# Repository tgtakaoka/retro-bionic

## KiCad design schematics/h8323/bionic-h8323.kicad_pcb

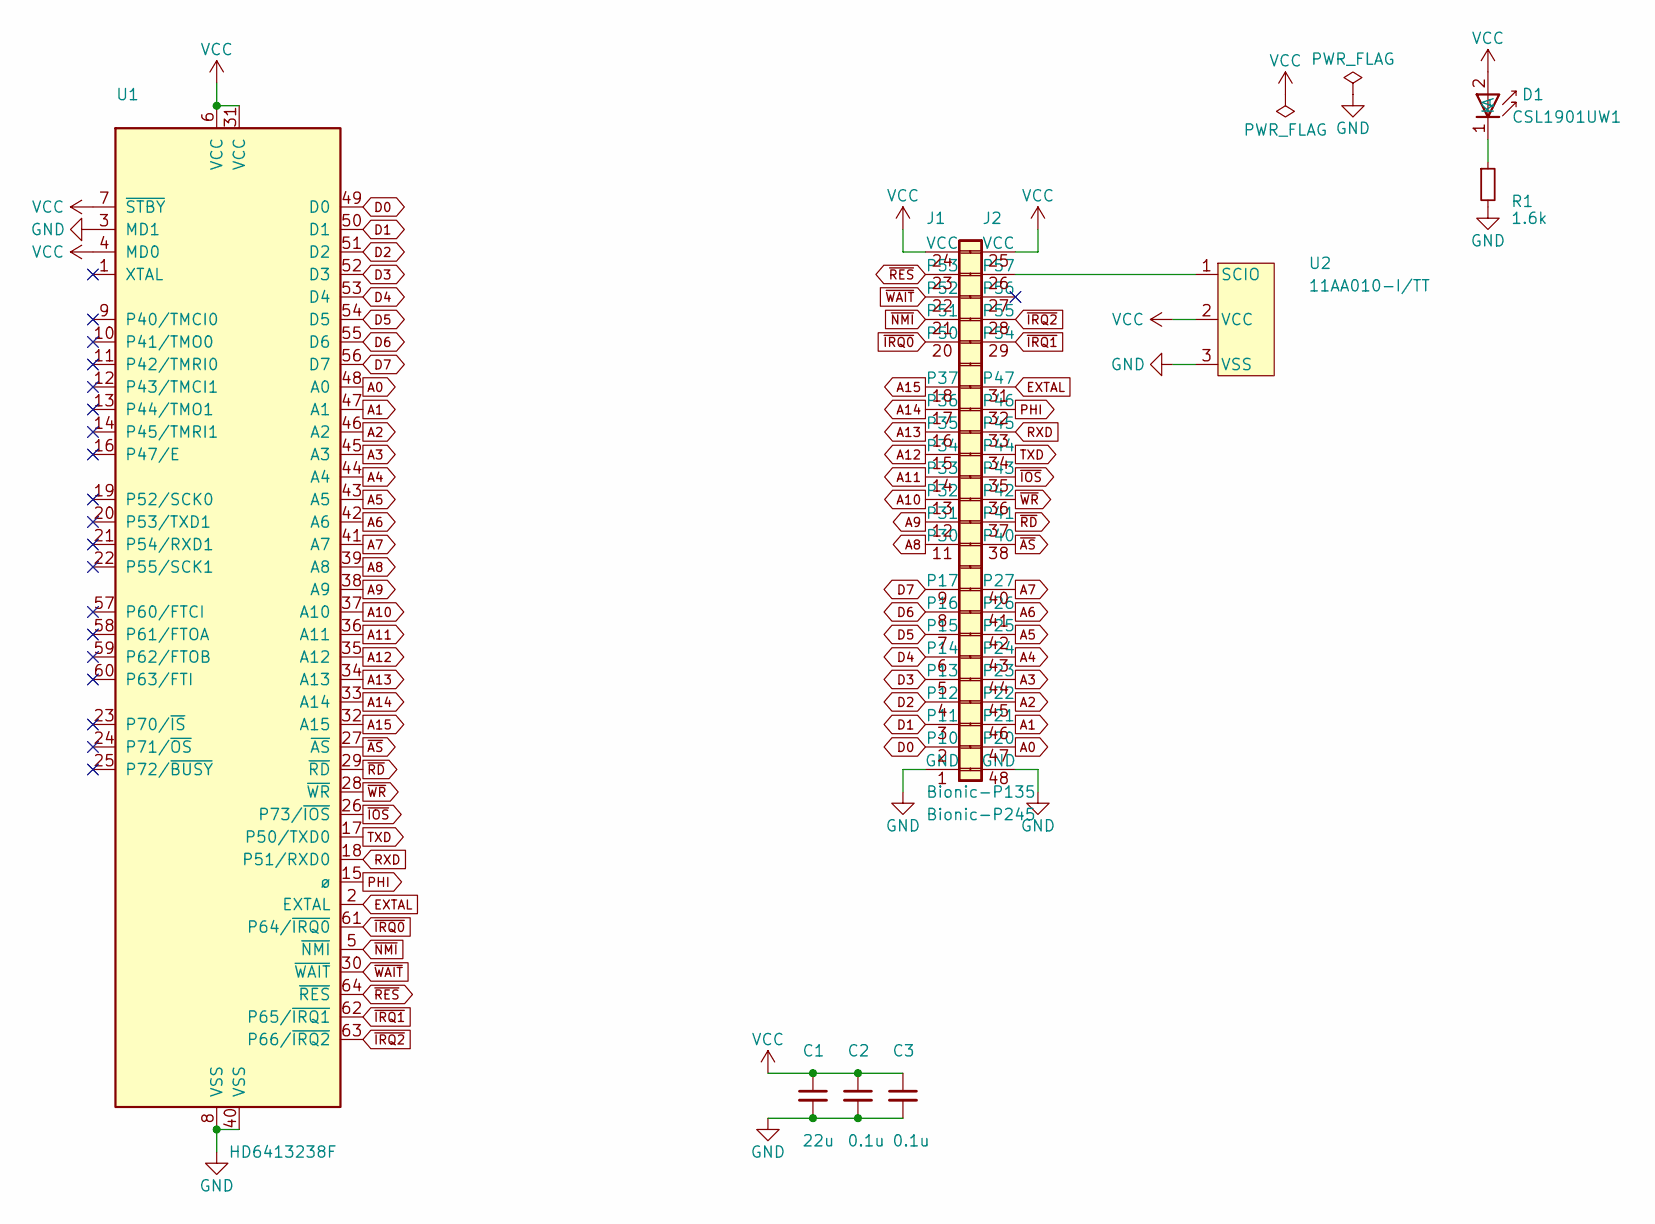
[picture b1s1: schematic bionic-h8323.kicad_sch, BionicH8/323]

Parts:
C1: 22u; C_0603_1608Metric_Pad1.08x0.95mm_HandSolder
C2, C3: 0.1u; C_0603_1608Metric_Pad1.08x0.95mm_HandSolder
D1: CSL1901UW1; LED_CSL1901UW1_ROM-M
J1: Bionic-P135; Bionic-P135_SMT
J2: Bionic-P245; Bionic-P245_SMT
R1: 1.6k; R_0603_1608Metric_Pad0.98x0.95mm_HandSolder
U1: HD6413238F; QFP-64_14x14mm_P0.8mm_Hitachi
U2: 11AA010-I/TT; SOT-23_MC_MCH-M

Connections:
A0: J2.47 (P20), U1.48 (A0)
A1: J2.46 (P21), U1.47 (A1)
A2: J2.45 (P22), U1.46 (A2)
A3: J2.44 (P23), U1.45 (A3)
A4: J2.43 (P24), U1.44 (A4)
A5: J2.42 (P25), U1.43 (A5)
A6: J2.41 (P26), U1.42 (A6)
A7: J2.40 (P27), U1.41 (A7)
A8: J1.11 (P30), U1.39 (A8)
A9: J1.12 (P31), U1.38 (A9)
A10: J1.13 (P32), U1.37 (A10)
A11: J1.14 (P33), U1.36 (A11)
A12: J1.15 (P34), U1.35 (A12)
A13: J1.16 (P35), U1.34 (A13)
A14: J1.17 (P36), U1.33 (A14)
A15: J1.18 (P37), U1.32 (A15)
D0: J1.2 (P10), U1.49 (D0)
D1: J1.3 (P11), U1.50 (D1)
D2: J1.4 (P12), U1.51 (D2)
D3: J1.5 (P13), U1.52 (D3)
D4: J1.6 (P14), U1.53 (D4)
D5: J1.7 (P15), U1.54 (D5)
D6: J1.8 (P16), U1.55 (D6)
D7: J1.9 (P17), U1.56 (D7)
EXTAL: J2.31 (P47), U1.2 (EXTAL)
GND: C1.2, C2.2, C3.2, J1.1 (GND), J2.48 (GND), R1.2, U1.3 (MD1), U1.8 (VSS), U1.40 (VSS), U2.3 (VSS)
unnamed: D1.1 (K), R1.1
unnamed: J2.26 (P57), U2.1 (SCIO)
PHI: J2.32 (P46), U1.15 (ø)
RXD: J2.33 (P45), U1.18 (P51/RXD0)
TXD: J2.34 (P44), U1.17 (P50/TXD0)
VCC: C1.1, C2.1, C3.1, D1.2 (A), J1.24 (VCC), J2.25 (VCC), U1.4 (MD0), U1.6 (VCC), U1.7 (~STBY), U1.31 (VCC), U2.2 (VCC)
~AS: J2.38 (P40), U1.27 (~AS)
~IOS: J2.35 (P43), U1.26 (P73/~IOS)
~IRQ0: J1.20 (P50), U1.61 (P64/~IRQ0)
~IRQ1: J2.29 (P54), U1.62 (P65/~IRQ1)
~IRQ2: J2.28 (P55), U1.63 (P66/~IRQ2)
~NMI: J1.21 (P51), U1.5 (~NMI)
~RD: J2.37 (P41), U1.29 (~RD)
~RES: J1.23 (P53), U1.64 (~RES)
~WAIT: J1.22 (P52), U1.30 (~WAIT)
~WR: J2.36 (P42), U1.28 (~WR)

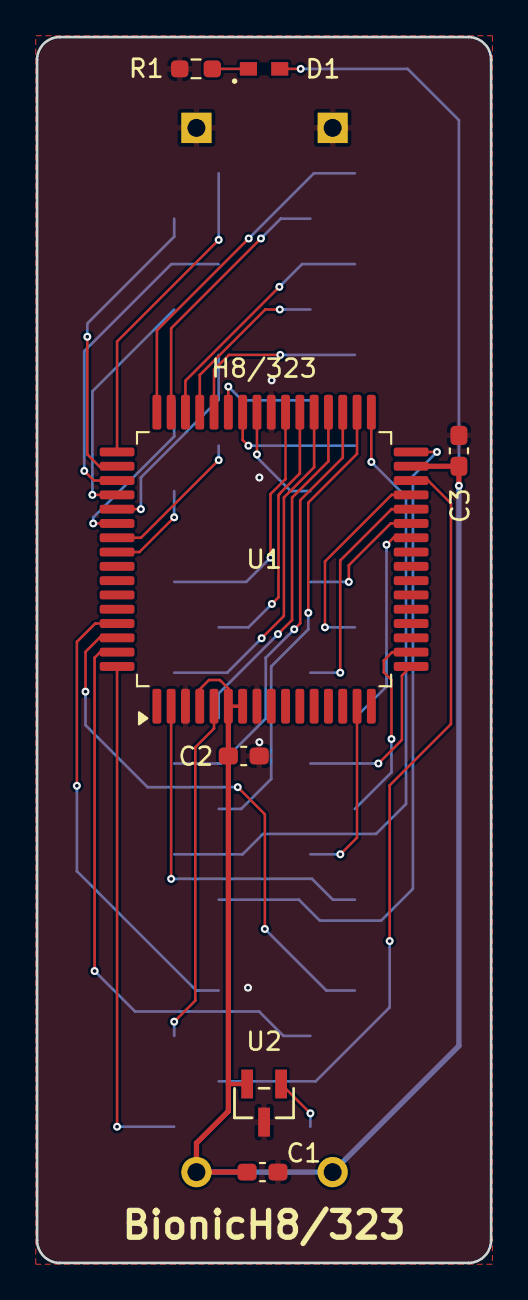
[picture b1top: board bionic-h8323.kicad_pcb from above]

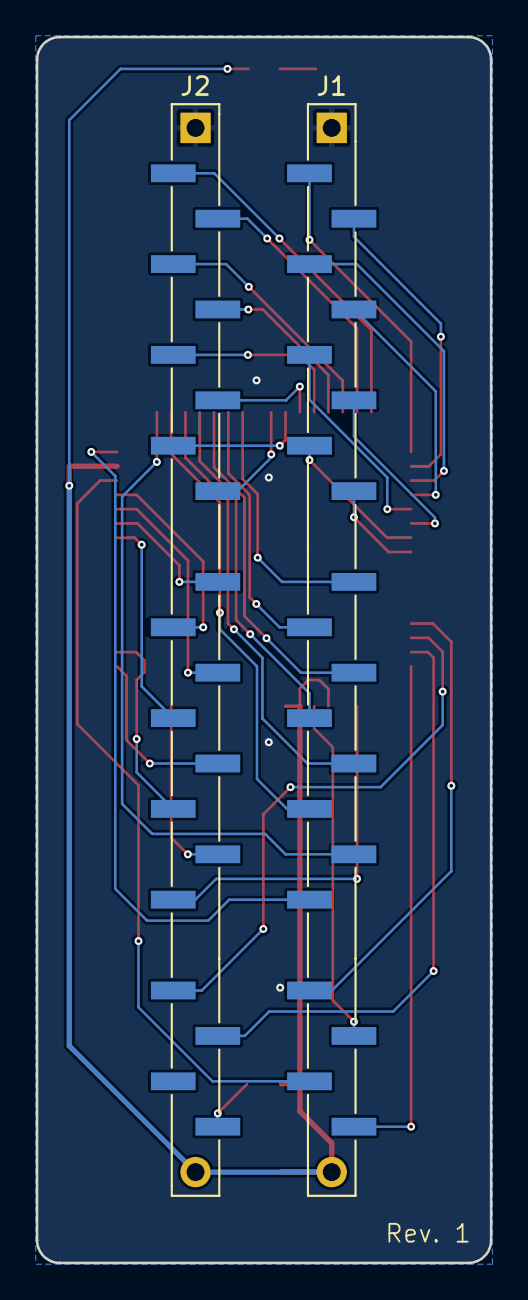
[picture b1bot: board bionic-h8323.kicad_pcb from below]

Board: 2 copper layers, 25.4 x 68.6 mm, 9 parts (2 on the bottom side), 42 nets.

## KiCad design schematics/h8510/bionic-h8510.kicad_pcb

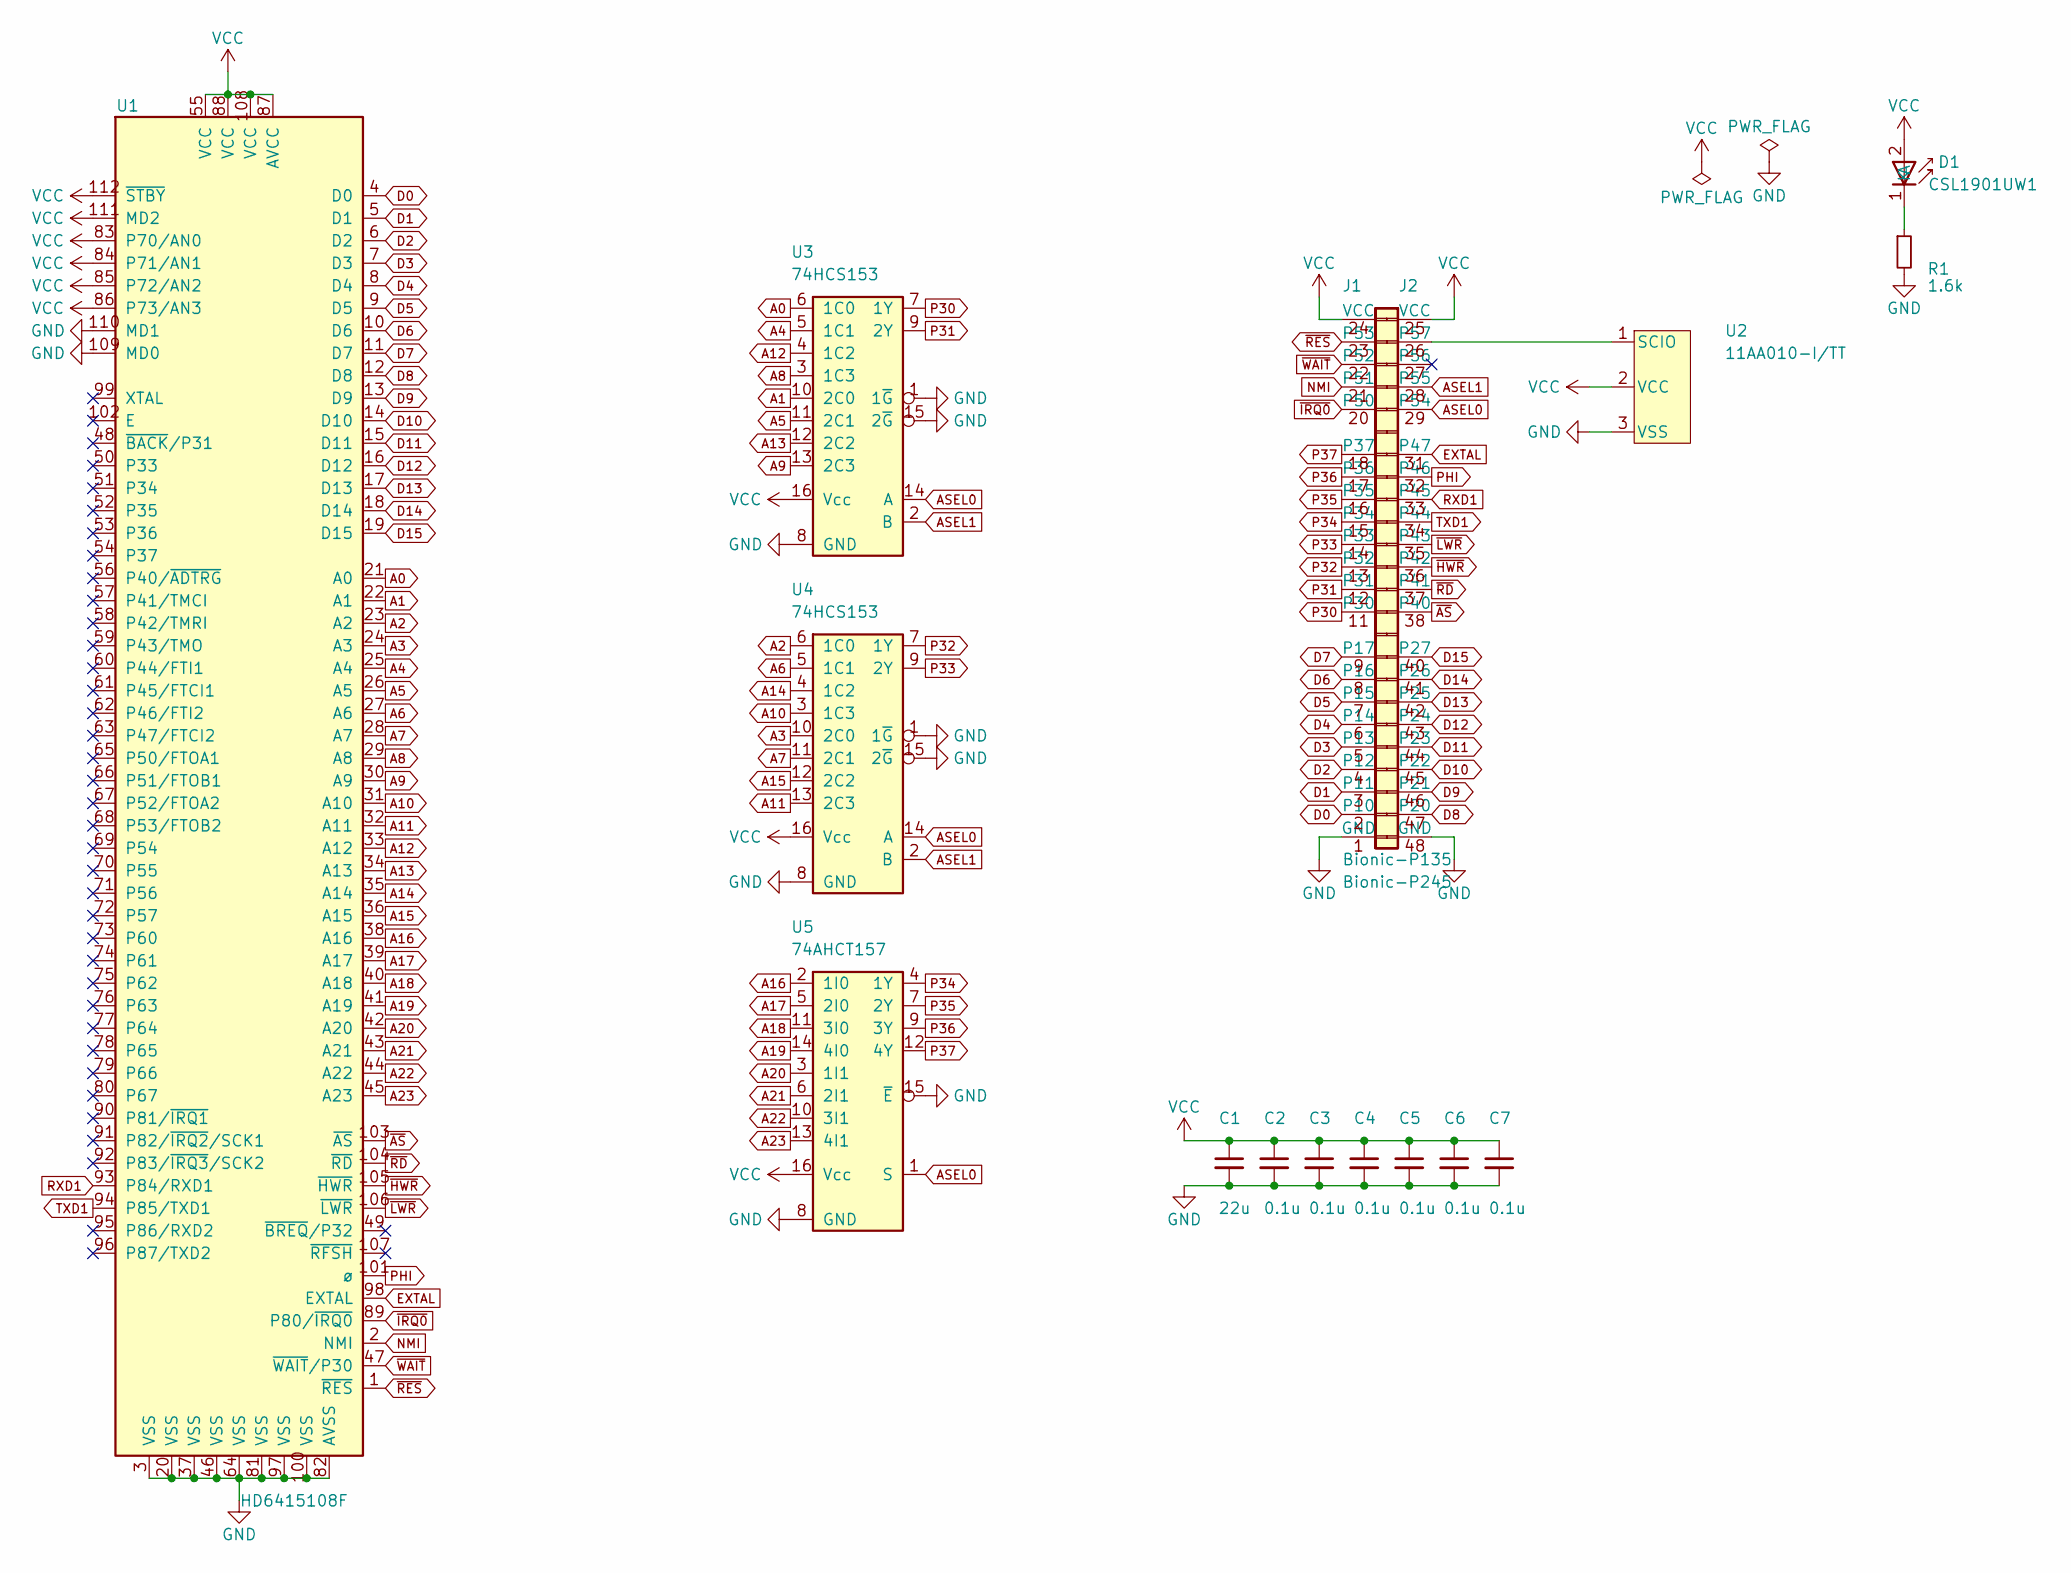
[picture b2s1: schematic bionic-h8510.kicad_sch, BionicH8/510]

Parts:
C1: 22u; C_0603_1608Metric_Pad1.08x0.95mm_HandSolder
C2, C3, C4, C5, C6, C7: 0.1u; C_0603_1608Metric_Pad1.08x0.95mm_HandSolder
D1: CSL1901UW1; LED_CSL1901UW1_ROM-M
J1: Bionic-P135; Bionic-P135_SMT
J2: Bionic-P245; Bionic-P245_SMT
R1: 1.6k; R_0603_1608Metric_Pad0.98x0.95mm_HandSolder
U1: HD6415108F; QFP-112_20x20mm_P0.65mm_Hitachi
U2: 11AA010-I/TT; SOT-23_MC_MCH-M
U3, U4: 74HCS153; PW16-M
U5: 74AHCT157; PW16-M

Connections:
A0: U1.21 (A0), U3.6 (1C0)
A1: U1.22 (A1), U3.10 (2C0)
A2: U1.23 (A2), U4.6 (1C0)
A3: U1.24 (A3), U4.10 (2C0)
A4: U1.25 (A4), U3.5 (1C1)
A5: U1.26 (A5), U3.11 (2C1)
A6: U1.27 (A6), U4.5 (1C1)
A7: U1.28 (A7), U4.11 (2C1)
A8: U1.29 (A8), U3.3 (1C3)
A9: U1.30 (A9), U3.13 (2C3)
A10: U1.31 (A10), U4.3 (1C3)
A11: U1.32 (A11), U4.13 (2C3)
A12: U1.33 (A12), U3.4 (1C2)
A13: U1.34 (A13), U3.12 (2C2)
A14: U1.35 (A14), U4.4 (1C2)
A15: U1.36 (A15), U4.12 (2C2)
A16: U1.38 (A16), U5.2 (1I0)
A17: U1.39 (A17), U5.5 (2I0)
A18: U1.40 (A18), U5.11 (3I0)
A19: U1.41 (A19), U5.14 (4I0)
A20: U1.42 (A20), U5.3 (1I1)
A21: U1.43 (A21), U5.6 (2I1)
A22: U1.44 (A22), U5.10 (3I1)
A23: U1.45 (A23), U5.13 (4I1)
ASEL0: J2.29 (P54), U3.14 (A), U4.14 (A), U5.1 (S)
ASEL1: J2.28 (P55), U3.2 (B), U4.2 (B)
D0: J1.2 (P10), U1.4 (D0)
D1: J1.3 (P11), U1.5 (D1)
D2: J1.4 (P12), U1.6 (D2)
D3: J1.5 (P13), U1.7 (D3)
D4: J1.6 (P14), U1.8 (D4)
D5: J1.7 (P15), U1.9 (D5)
D6: J1.8 (P16), U1.10 (D6)
D7: J1.9 (P17), U1.11 (D7)
D8: J2.47 (P20), U1.12 (D8)
D9: J2.46 (P21), U1.13 (D9)
D10: J2.45 (P22), U1.14 (D10)
D11: J2.44 (P23), U1.15 (D11)
D12: J2.43 (P24), U1.16 (D12)
D13: J2.42 (P25), U1.17 (D13)
D14: J2.41 (P26), U1.18 (D14)
D15: J2.40 (P27), U1.19 (D15)
EXTAL: J2.31 (P47), U1.98 (EXTAL)
GND: C1.2, C2.2, C3.2, C4.2, C5.2, C6.2, C7.2, J1.1 (GND), J2.48 (GND), R1.2, U1.3 (VSS), U1.20 (VSS), U1.37 (VSS), U1.46 (VSS), U1.64 (VSS), U1.81 (VSS), U1.82 (AVSS), U1.97 (VSS), U1.100 (VSS), U1.109 (MD0), U1.110 (MD1), U2.3 (VSS), U3.1 (1~G), U3.8 (GND), U3.15 (2~G), U4.1 (1~G), U4.8 (GND), U4.15 (2~G), U5.8 (GND), U5.15 (~E)
NMI: J1.21 (P51), U1.2 (NMI)
unnamed: D1.1 (K), R1.1
unnamed: J2.26 (P57), U2.1 (SCIO)
P30: J1.11 (P30), U3.7 (1Y)
P31: J1.12 (P31), U3.9 (2Y)
P32: J1.13 (P32), U4.7 (1Y)
P33: J1.14 (P33), U4.9 (2Y)
P34: J1.15 (P34), U5.4 (1Y)
P35: J1.16 (P35), U5.7 (2Y)
P36: J1.17 (P36), U5.9 (3Y)
P37: J1.18 (P37), U5.12 (4Y)
PHI: J2.32 (P46), U1.101 (ø)
RXD1: J2.33 (P45), U1.93 (P84/RXD1)
TXD1: J2.34 (P44), U1.94 (P85/TXD1)
VCC: C1.1, C2.1, C3.1, C4.1, C5.1, C6.1, C7.1, D1.2 (A), J1.24 (VCC), J2.25 (VCC), U1.55 (VCC), U1.83 (P70/AN0), U1.84 (P71/AN1), U1.85 (P72/AN2), U1.86 (P73/AN3), U1.87 (AVCC), U1.88 (VCC), U1.108 (VCC), U1.111 (MD2), U1.112 (~STBY), U2.2 (VCC), U3.16 (Vcc), U4.16 (Vcc), U5.16 (Vcc)
~AS: J2.38 (P40), U1.103 (~AS)
~HWR: J2.36 (P42), U1.105 (~HWR)
~IRQ0: J1.20 (P50), U1.89 (P80/~IRQ0)
~LWR: J2.35 (P43), U1.106 (~LWR)
~RD: J2.37 (P41), U1.104 (~RD)
~RES: J1.23 (P53), U1.1 (~RES)
~WAIT: J1.22 (P52), U1.47 (~WAIT/P30)

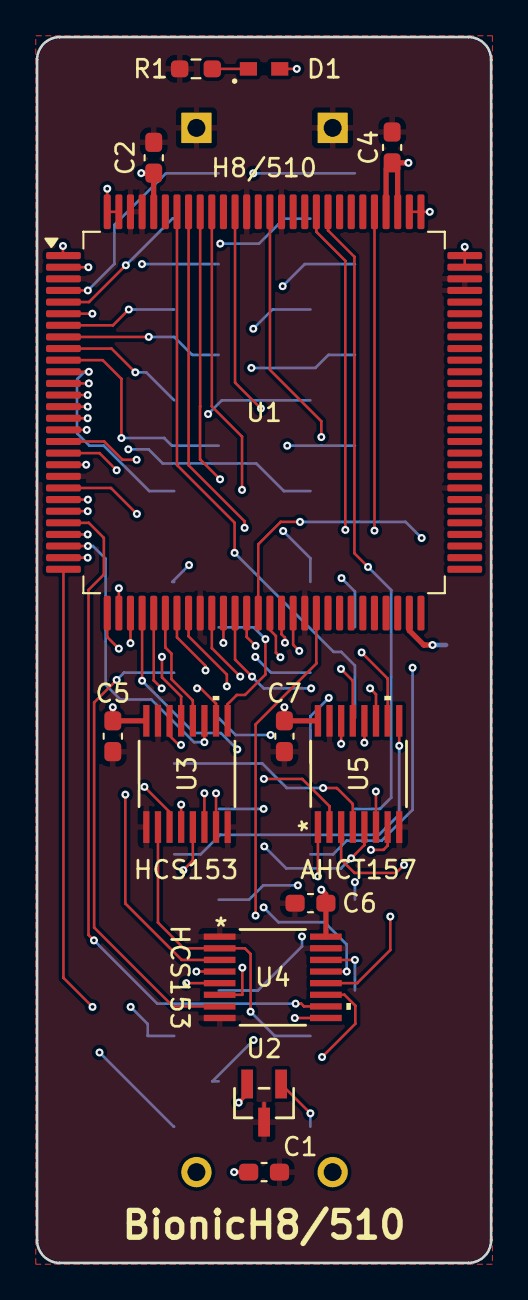
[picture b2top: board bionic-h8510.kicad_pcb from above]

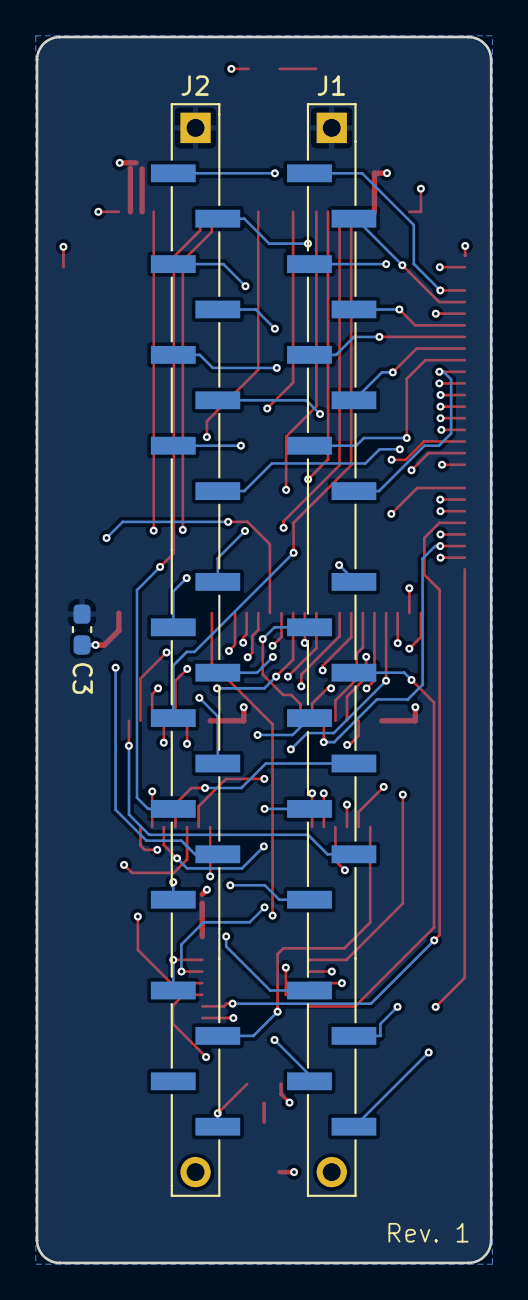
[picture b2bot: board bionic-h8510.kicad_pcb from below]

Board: 4 copper layers, 25.4 x 68.6 mm, 16 parts (3 on the bottom side), 66 nets.

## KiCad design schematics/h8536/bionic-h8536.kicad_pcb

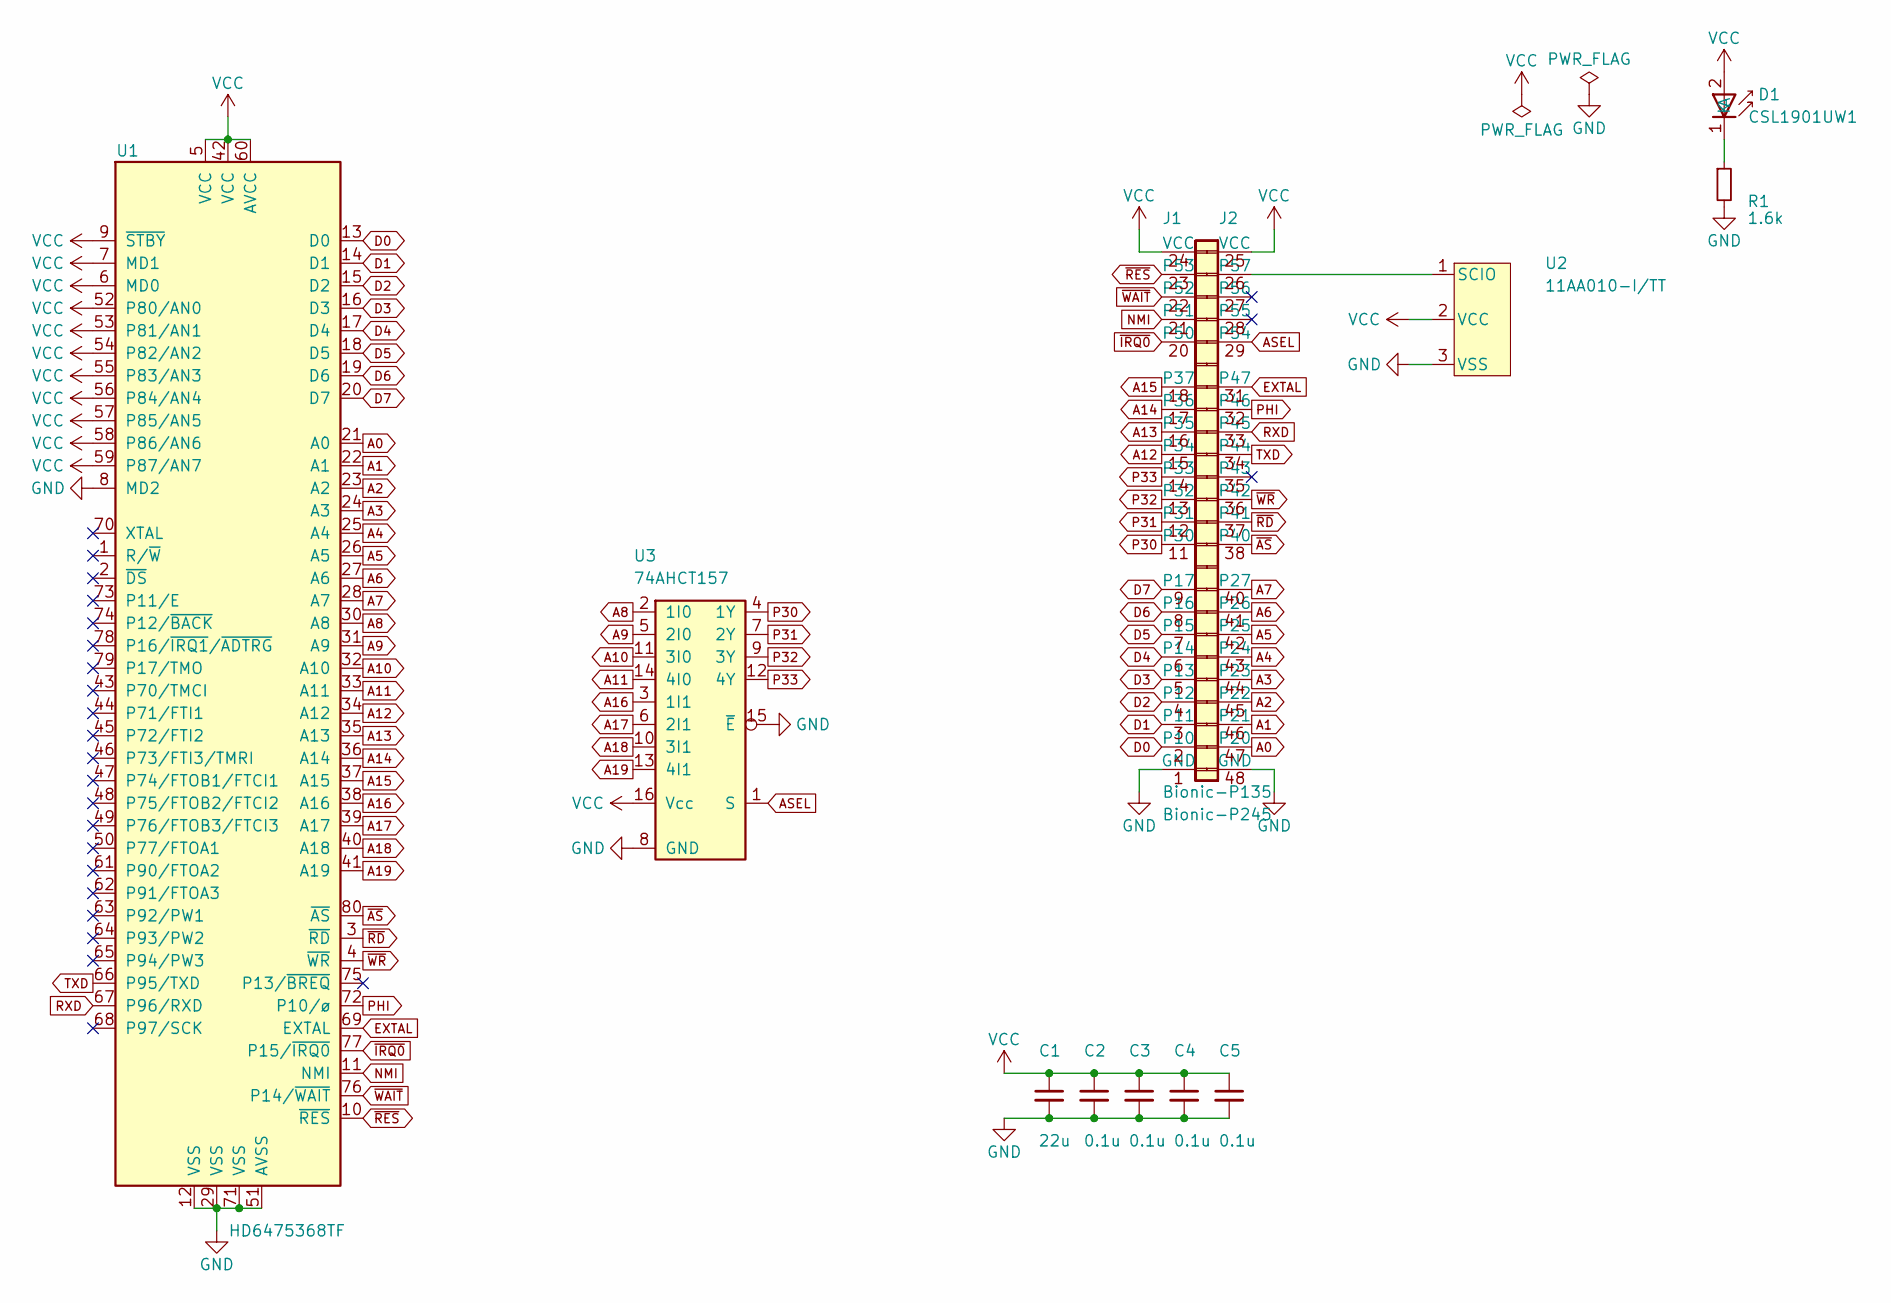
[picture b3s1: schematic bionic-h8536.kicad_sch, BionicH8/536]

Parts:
C1: 22u; C_0603_1608Metric_Pad1.08x0.95mm_HandSolder
C2, C3, C4, C5: 0.1u; C_0603_1608Metric_Pad1.08x0.95mm_HandSolder
D1: CSL1901UW1; LED_CSL1901UW1_ROM-M
J1: Bionic-P135; Bionic-P135_SMT
J2: Bionic-P245; Bionic-P245_SMT
R1: 1.6k; R_0603_1608Metric_Pad0.98x0.95mm_HandSolder
U1: HD6475368TF; TQFP-80_12x12mm_P0.5mm_Hitachi
U2: 11AA010-I/TT; SOT-23_MC_MCH-M
U3: 74AHCT157; PW16-M

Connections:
A0: J2.47 (P20), U1.21 (A0)
A1: J2.46 (P21), U1.22 (A1)
A2: J2.45 (P22), U1.23 (A2)
A3: J2.44 (P23), U1.24 (A3)
A4: J2.43 (P24), U1.25 (A4)
A5: J2.42 (P25), U1.26 (A5)
A6: J2.41 (P26), U1.27 (A6)
A7: J2.40 (P27), U1.28 (A7)
A8: U1.30 (A8), U3.2 (1I0)
A9: U1.31 (A9), U3.5 (2I0)
A10: U1.32 (A10), U3.11 (3I0)
A11: U1.33 (A11), U3.14 (4I0)
A12: J1.15 (P34), U1.34 (A12)
A13: J1.16 (P35), U1.35 (A13)
A14: J1.17 (P36), U1.36 (A14)
A15: J1.18 (P37), U1.37 (A15)
A16: U1.38 (A16), U3.3 (1I1)
A17: U1.39 (A17), U3.6 (2I1)
A18: U1.40 (A18), U3.10 (3I1)
A19: U1.41 (A19), U3.13 (4I1)
ASEL: J2.29 (P54), U3.1 (S)
D0: J1.2 (P10), U1.13 (D0)
D1: J1.3 (P11), U1.14 (D1)
D2: J1.4 (P12), U1.15 (D2)
D3: J1.5 (P13), U1.16 (D3)
D4: J1.6 (P14), U1.17 (D4)
D5: J1.7 (P15), U1.18 (D5)
D6: J1.8 (P16), U1.19 (D6)
D7: J1.9 (P17), U1.20 (D7)
EXTAL: J2.31 (P47), U1.69 (EXTAL)
GND: C1.2, C2.2, C3.2, C4.2, C5.2, J1.1 (GND), J2.48 (GND), R1.2, U1.8 (MD2), U1.12 (VSS), U1.29 (VSS), U1.51 (AVSS), U1.71 (VSS), U2.3 (VSS), U3.8 (GND), U3.15 (~E)
NMI: J1.21 (P51), U1.11 (NMI)
unnamed: D1.1 (K), R1.1
unnamed: J2.26 (P57), U2.1 (SCIO)
P30: J1.11 (P30), U3.4 (1Y)
P31: J1.12 (P31), U3.7 (2Y)
P32: J1.13 (P32), U3.9 (3Y)
P33: J1.14 (P33), U3.12 (4Y)
PHI: J2.32 (P46), U1.72 (P10/ø)
RXD: J2.33 (P45), U1.67 (P96/RXD)
TXD: J2.34 (P44), U1.66 (P95/TXD)
VCC: C1.1, C2.1, C3.1, C4.1, C5.1, D1.2 (A), J1.24 (VCC), J2.25 (VCC), U1.5 (VCC), U1.6 (MD0), U1.7 (MD1), U1.9 (~STBY), U1.42 (VCC), U1.52 (P80/AN0), U1.53 (P81/AN1), U1.54 (P82/AN2), U1.55 (P83/AN3), U1.56 (P84/AN4), U1.57 (P85/AN5), U1.58 (P86/AN6), U1.59 (P87/AN7), U1.60 (AVCC), U2.2 (VCC), U3.16 (Vcc)
~AS: J2.38 (P40), U1.80 (~AS)
~IRQ0: J1.20 (P50), U1.77 (P15/~IRQ0)
~RD: J2.37 (P41), U1.3 (~RD)
~RES: J1.23 (P53), U1.10 (~RES)
~WAIT: J1.22 (P52), U1.76 (P14/~WAIT)
~WR: J2.36 (P42), U1.4 (~WR)

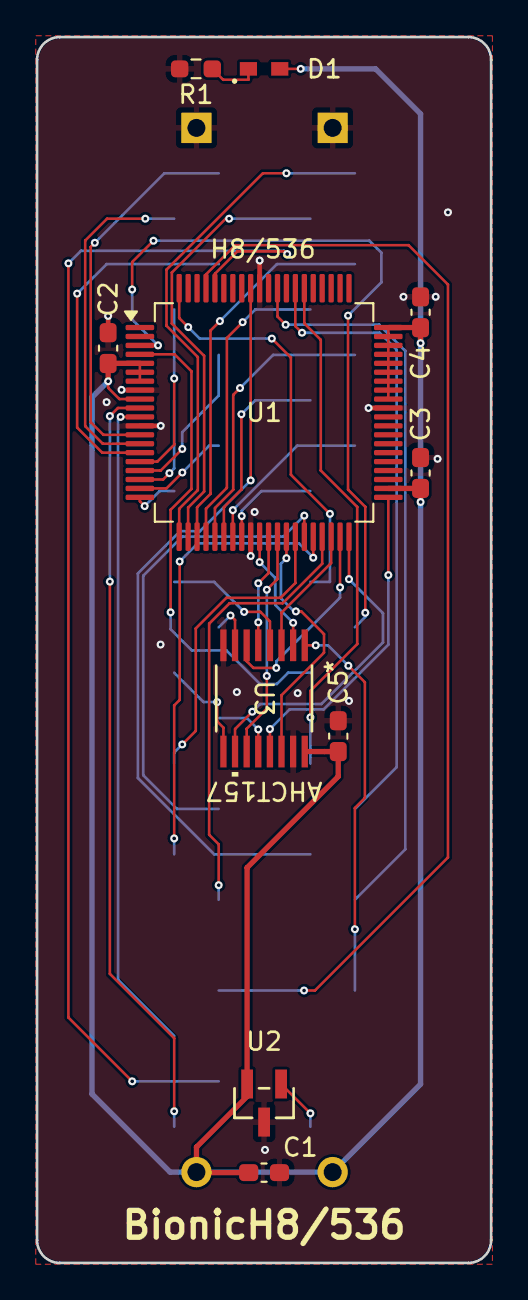
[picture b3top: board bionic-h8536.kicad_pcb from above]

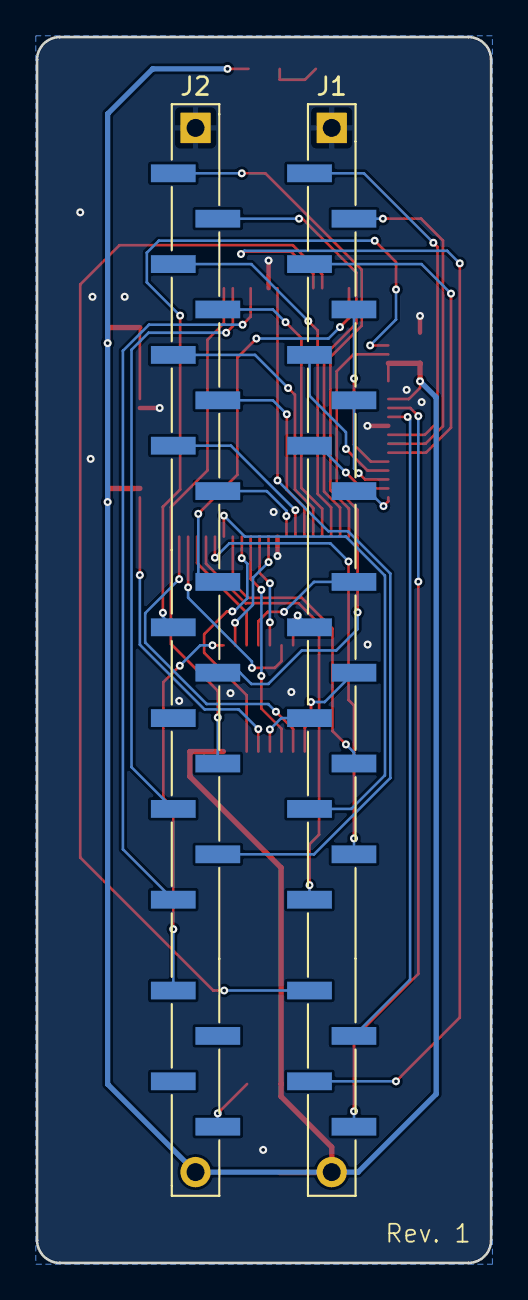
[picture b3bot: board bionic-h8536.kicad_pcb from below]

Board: 2 copper layers, 25.4 x 68.6 mm, 12 parts (2 on the bottom side), 48 nets.

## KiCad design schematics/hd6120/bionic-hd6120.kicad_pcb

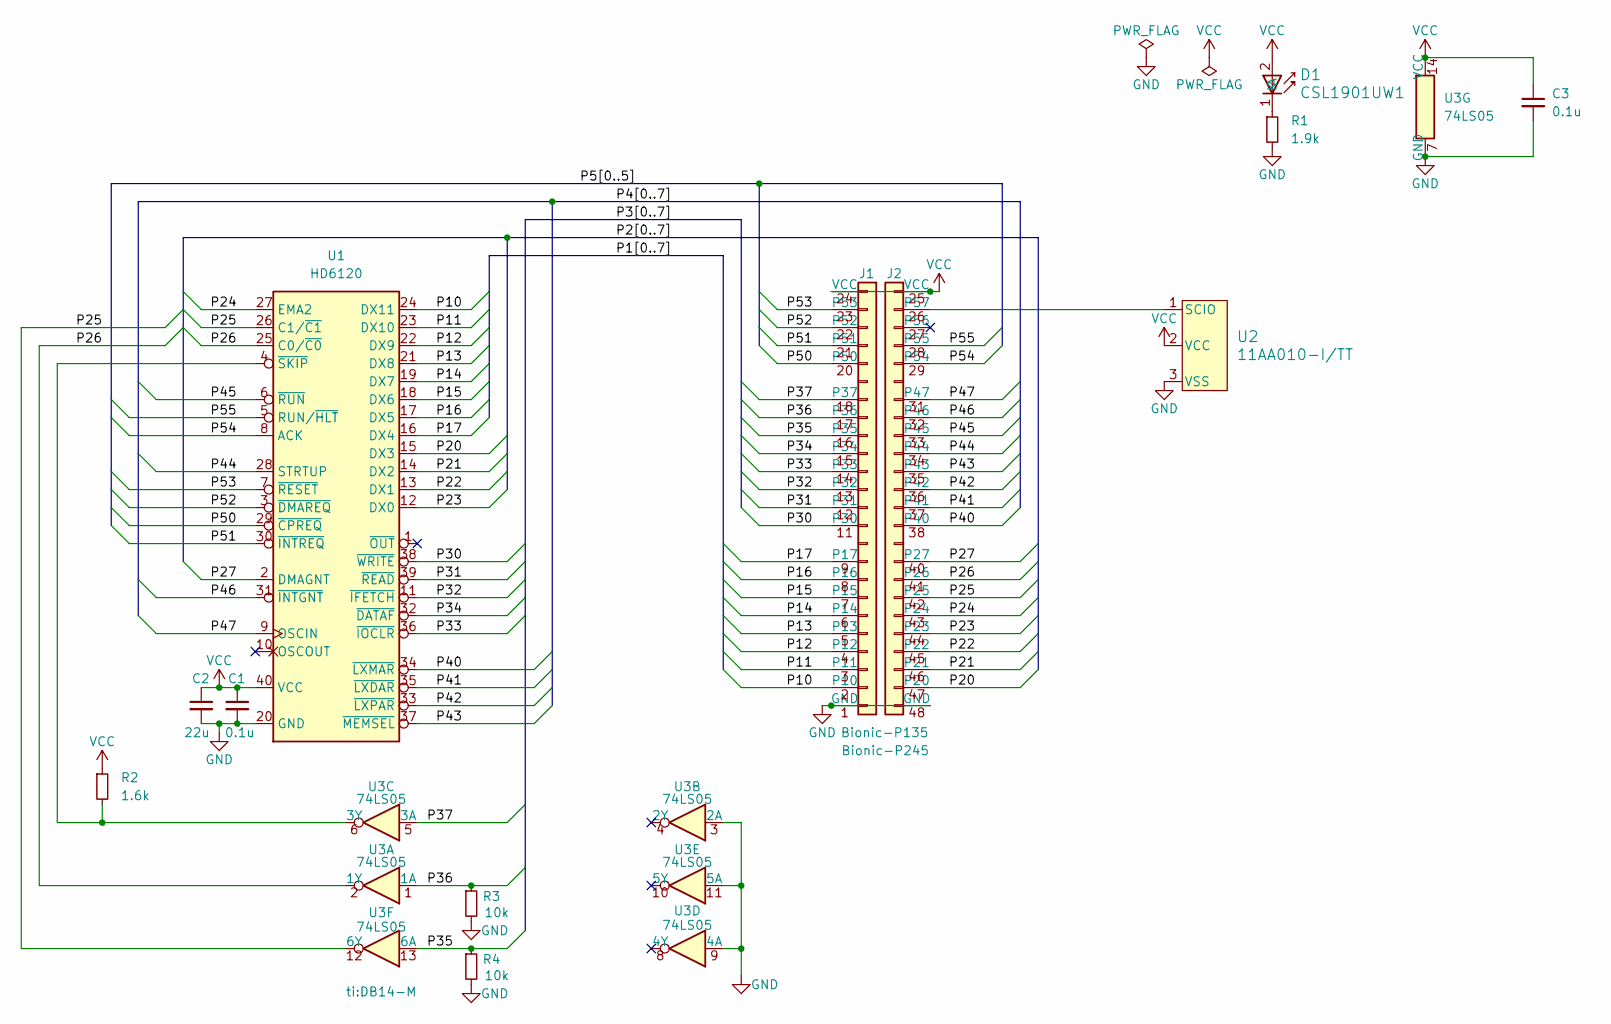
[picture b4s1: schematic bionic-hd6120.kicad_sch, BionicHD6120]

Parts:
C1, C3: 0.1u; C_0603_1608Metric_Pad1.08x0.95mm_HandSolder
C2: 22u; C_0603_1608Metric_Pad1.08x0.95mm_HandSolder
D1: CSL1901UW1; LED_CSL1901UW1_ROM-M
J1: Bionic-P135; Bionic-P135_THT
J2: Bionic-P245; Bionic-P245_THT
R1: 1.9k; R_0603_1608Metric_Pad0.98x0.95mm_HandSolder
R2: 1.6k; R_0603_1608Metric_Pad0.98x0.95mm_HandSolder
R3, R4: 10k; R_0603_1608Metric_Pad0.98x0.95mm_HandSolder
U1: HD6120; DIP-40_W15.24mm_Socket
U2: 11AA010-I/TT; SOT-23_MC_MCH-M
U3: 74LS05; DB14-M

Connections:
/P10: J1.2 (P10), U1.24 (DX11)
/P11: J1.3 (P11), U1.23 (DX10)
/P12: J1.4 (P12), U1.22 (DX9)
/P13: J1.5 (P13), U1.21 (DX8)
/P14: J1.6 (P14), U1.19 (DX7)
/P15: J1.7 (P15), U1.18 (DX6)
/P16: J1.8 (P16), U1.17 (DX5)
/P17: J1.9 (P17), U1.16 (DX4)
/P20: J2.47 (P20), U1.15 (DX3)
/P21: J2.46 (P21), U1.14 (DX2)
/P22: J2.45 (P22), U1.13 (DX1)
/P23: J2.44 (P23), U1.12 (DX0)
/P24: J2.43 (P24), U1.27 (EMA2)
/P25: J2.42 (P25), U1.26 (C1/~C1), U3.12 (6Y)
/P26: J2.41 (P26), U1.25 (C0/~C0), U3.2 (1Y)
/P27: J2.40 (P27), U1.2 (DMAGNT)
/P30: J1.11 (P30), U1.38 (~WRITE)
/P31: J1.12 (P31), U1.39 (~READ)
/P32: J1.13 (P32), U1.11 (~IFETCH)
/P33: J1.14 (P33), U1.36 (~IOCLR)
/P34: J1.15 (P34), U1.32 (~DATAF)
/P35: J1.16 (P35), R4.1, U3.13 (6A)
/P36: J1.17 (P36), R3.1, U3.1 (1A)
/P37: J1.18 (P37), U3.5 (3A)
/P40: J2.38 (P40), U1.34 (~LXMAR)
/P41: J2.37 (P41), U1.35 (~LXDAR)
/P42: J2.36 (P42), U1.33 (~LXPAR)
/P43: J2.35 (P43), U1.37 (~MEMSEL)
/P44: J2.34 (P44), U1.28 (STRTUP)
/P45: J2.33 (P45), U1.6 (~RUN)
/P46: J2.32 (P46), U1.31 (~INTGNT)
/P47: J2.31 (P47), U1.9 (OSCIN)
/P50: J1.20 (P50), U1.29 (~CPREQ)
/P51: J1.21 (P51), U1.30 (~INTREQ)
/P52: J1.22 (P52), U1.3 (~DMAREQ)
/P53: J1.23 (P53), U1.7 (~RESET)
/P54: J2.29 (P54), U1.8 (ACK)
/P55: J2.28 (P55), U1.5 (RUN/~HLT)
GND: C1.2, C2.2, C3.2, J1.1 (GND), J2.48 (GND), R1.2, R3.2, R4.2, U1.20 (GND), U2.3 (VSS), U3.3 (2A), U3.7 (GND), U3.9 (4A), U3.11 (5A)
unnamed: D1.1 (K), R1.1
unnamed: J2.26 (P57), U2.1 (SCIO)
unnamed: R2.2, U1.4 (~SKIP), U3.6 (3Y)
VCC: C1.1, C2.1, C3.1, D1.2 (A), J1.24 (VCC), J2.25 (VCC), R2.1, U1.40 (VCC), U2.2 (VCC), U3.14 (VCC)

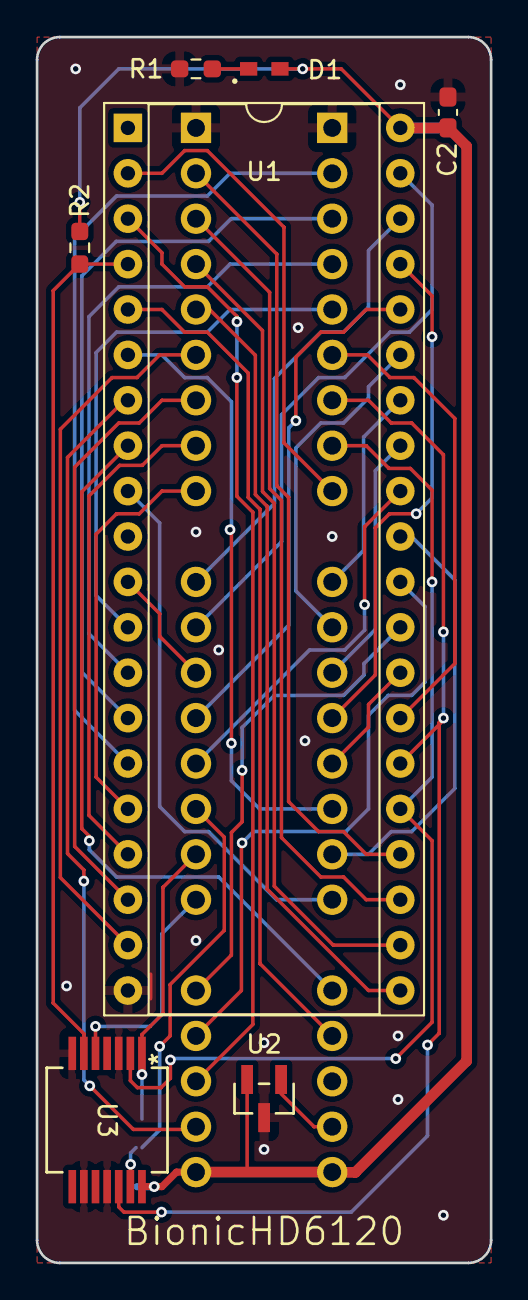
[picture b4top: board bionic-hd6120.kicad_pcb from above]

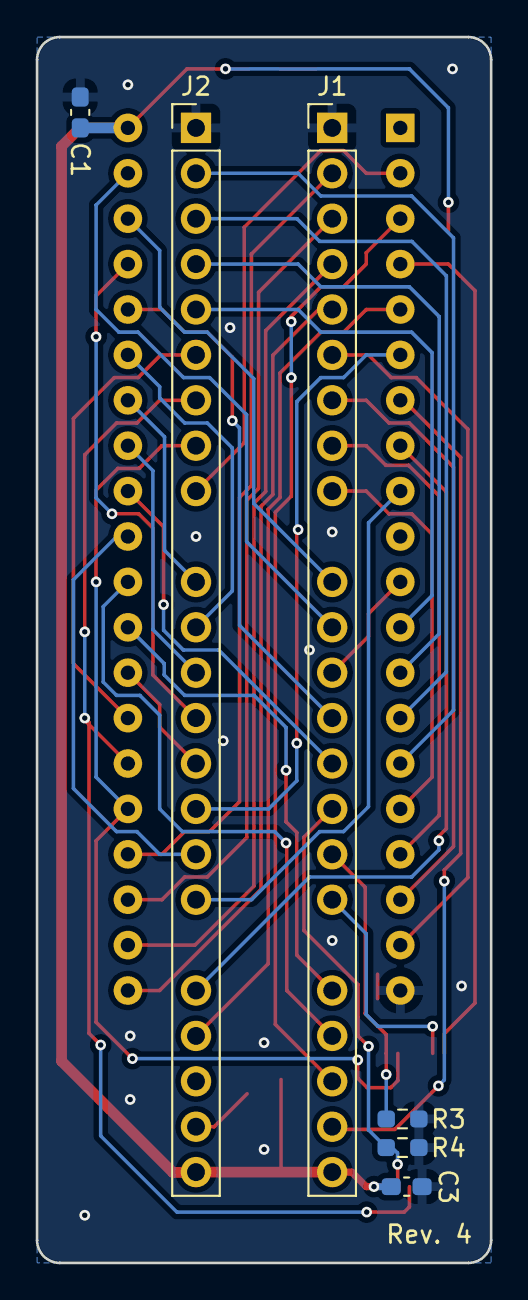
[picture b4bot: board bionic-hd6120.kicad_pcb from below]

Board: 2 copper layers, 25.4 x 68.6 mm, 13 parts (6 on the bottom side), 43 nets.
